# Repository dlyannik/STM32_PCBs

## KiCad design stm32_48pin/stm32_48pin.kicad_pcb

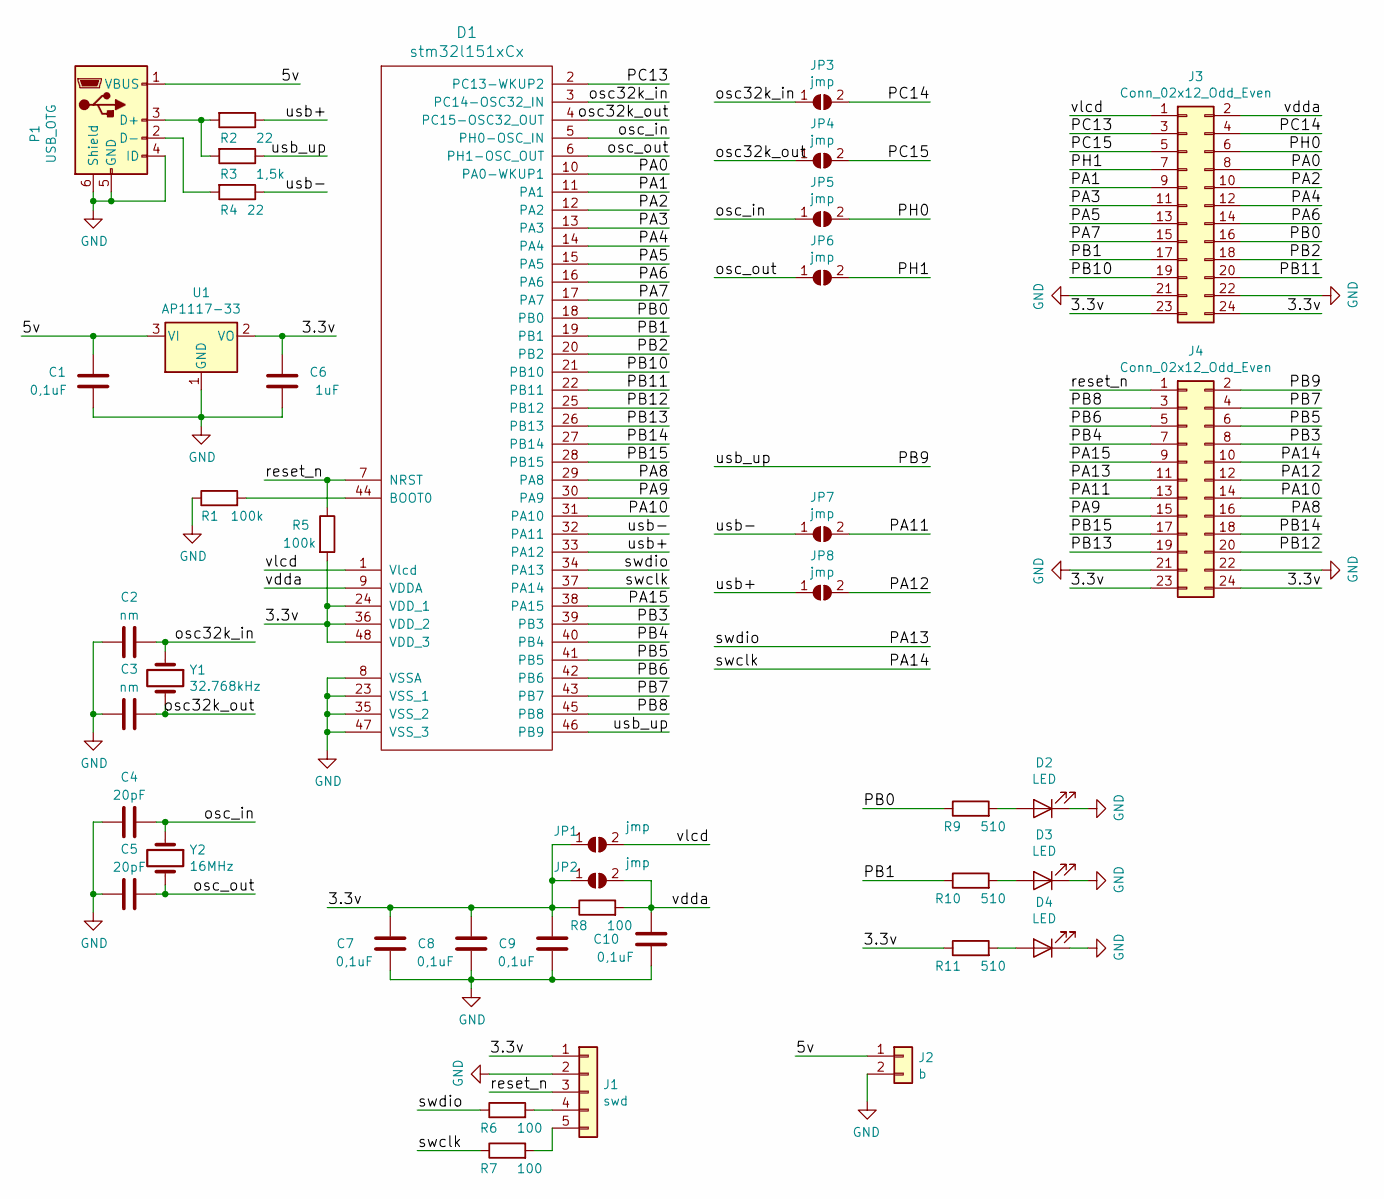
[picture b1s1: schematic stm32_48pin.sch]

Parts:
C1, C7, C8, C9, C10: 0,1uF; C_0603_1608Metric
C2, C3: nm; C_0603_1608Metric
C4, C5: 20pF; C_0603_1608Metric
C6: 1uF; C_0603_1608Metric
D1: stm32l151xCx; LQFP-48_7x7mm_P0.5mm
D2, D3, D4: LED; LED_0603_1608Metric
J1: swd; PinHeader_1x05_P2.54mm_Vertical
J2: b; PinHeader_1x02_P2.54mm_Vertical
J3, J4: Conn_02x12_Odd_Even; PinHeader_2x12_P2.54mm_Vertical
JP1, JP2, JP3, JP4, JP5, JP6, JP7, JP8: jmp; SolderJumper-2_P1.3mm_Open_TrianglePad1.0x1.5mm
P1: USB_OTG; USB_Mini-B_Lumberg_2486_01_Horizontal
R1, R5: 100k; R_0603_1608Metric
R2, R4: 22; R_0603_1608Metric
R3: 1,5k; R_0603_1608Metric
R6, R7, R8: 100; R_0603_1608Metric
R9, R10, R11: 510; R_0603_1608Metric
U1: AP1117-33; SOT-223-3_TabPin2
Y1: 32.768kHz; Crystal_DS26_D2.0mm_L6.0mm_Horizontal
Y2: 16MHz; Crystal_HC18-U_Vertical

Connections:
/3.3v: C6.1, C7.1, C8.1, C9.1, D1.24 (VDD_1), D1.36 (VDD_2), D1.48 (VDD_3), J1.1, J3.23, J3.24, J4.23, J4.24, JP1.1 (A), JP2.1 (A), R5.2, R8.1, R11.1, U1.2 (VO)
/5v: C1.1, J2.1, P1.1 (VBUS), U1.3 (VI)
/PA0: D1.10 (PA0-WKUP1), J3.8
/PA1: D1.11 (PA1), J3.9
/PA2: D1.12 (PA2), J3.10
/PA3: D1.13 (PA3), J3.11
/PA4: D1.14 (PA4), J3.12
/PA5: D1.15 (PA5), J3.13
/PA6: D1.16 (PA6), J3.14
/PA7: D1.17 (PA7), J3.15
/PA8: D1.29 (PA8), J4.16
/PA9: D1.30 (PA9), J4.15
/PA10: D1.31 (PA10), J4.14
/PA11: J4.13, JP7.2 (B)
/PA12: J4.12, JP8.2 (B)
/PA13: D1.34 (PA13), J4.11, R6.1
/PA14: D1.37 (PA14), J4.10, R7.1
/PA15: D1.38 (PA15), J4.9
/PB0: D1.18 (PB0), J3.16, R9.1
/PB1: D1.19 (PB1), J3.17, R10.1
/PB2: D1.20 (PB2), J3.18
/PB3: D1.39 (PB3), J4.8
/PB4: D1.40 (PB4), J4.7
/PB5: D1.41 (PB5), J4.6
/PB6: D1.42 (PB6), J4.5
/PB7: D1.43 (PB7), J4.4
/PB8: D1.45 (PB8), J4.3
/PB9: D1.46 (PB9), J4.2, R3.1
/PB10: D1.21 (PB10), J3.19
/PB11: D1.22 (PB11), J3.20
/PB12: D1.25 (PB12), J4.20
/PB13: D1.26 (PB13), J4.19
/PB14: D1.27 (PB14), J4.18
/PB15: D1.28 (PB15), J4.17
/PC13: D1.2 (PC13-WKUP2), J3.3
/PC14: J3.4, JP3.2 (B)
/PC15: J3.5, JP4.2 (B)
/PH0: J3.6, JP5.2 (B)
/PH1: J3.7, JP6.2 (B)
/osc32k_in: C2.1, D1.3 (PC14-OSC32_IN), JP3.1 (A), Y1.1
/osc32k_out: C3.1, D1.4 (PC15-OSC32_OUT), JP4.1 (A), Y1.2
/osc_in: C4.1, D1.5 (PH0-OSC_IN), JP5.1 (A), Y2.1
/osc_out: C5.1, D1.6 (PH1-OSC_OUT), JP6.1 (A), Y2.2
/reset_n: D1.7 (NRST), J1.3, J4.1, R5.1
/usb+: D1.33 (PA12), JP8.1 (A), R2.1
/usb-: D1.32 (PA11), JP7.1 (A), R4.1
/vdda: C10.1, D1.9 (VDDA), J3.2, JP2.2 (B), R8.2
/vlcd: D1.1 (Vlcd), J3.1, JP1.2 (B)
GND: C1.2, C2.2, C3.2, C4.2, C5.2, C6.2, C7.2, C8.2, C9.2, C10.2, D1.8 (VSSA), D1.23 (VSS_1), D1.35 (VSS_2), D1.47 (VSS_3), D2.1 (K), D3.1 (K), D4.1 (K), J1.2, J2.2, J3.21, J3.22, J4.21, J4.22, P1.4 (ID), P1.5 (GND), P1.6 (Shield), R1.1, U1.1 (GND)
unnamed: D1.44 (BOOT0), R1.2
unnamed: D2.2 (A), R9.2
unnamed: D3.2 (A), R10.2
unnamed: D4.2 (A), R11.2
unnamed: J1.4, R6.2
unnamed: J1.5, R7.2
unnamed: P1.2 (D-), R4.2
unnamed: P1.3 (D+), R2.2, R3.2

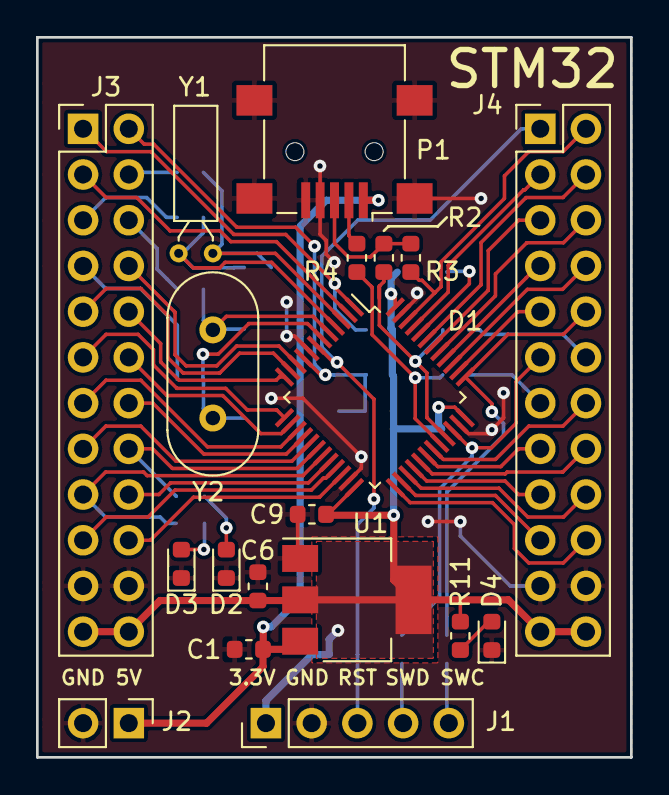
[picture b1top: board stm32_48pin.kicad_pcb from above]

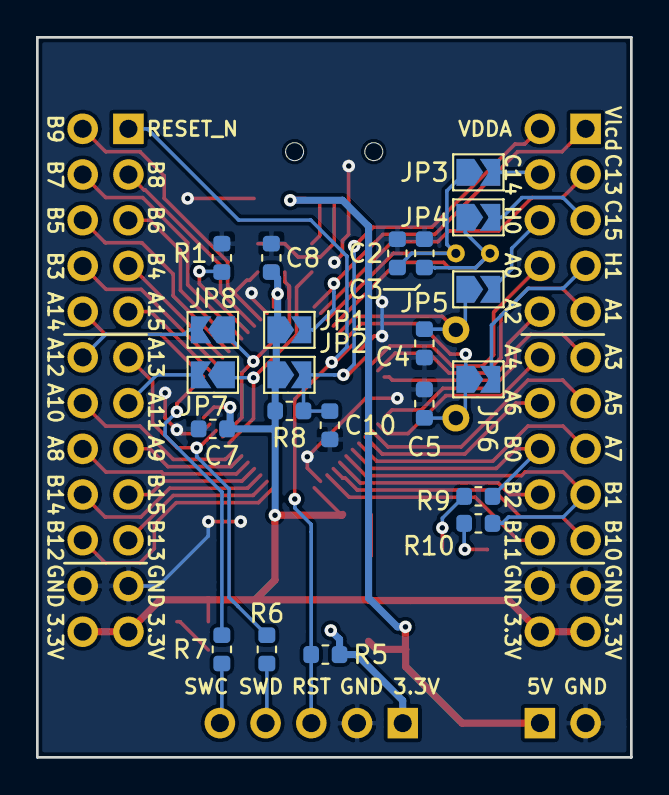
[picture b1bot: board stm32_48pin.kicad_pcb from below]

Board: 2 copper layers, 33.0 x 40.0 mm, 41 parts (22 on the bottom side), 57 nets.

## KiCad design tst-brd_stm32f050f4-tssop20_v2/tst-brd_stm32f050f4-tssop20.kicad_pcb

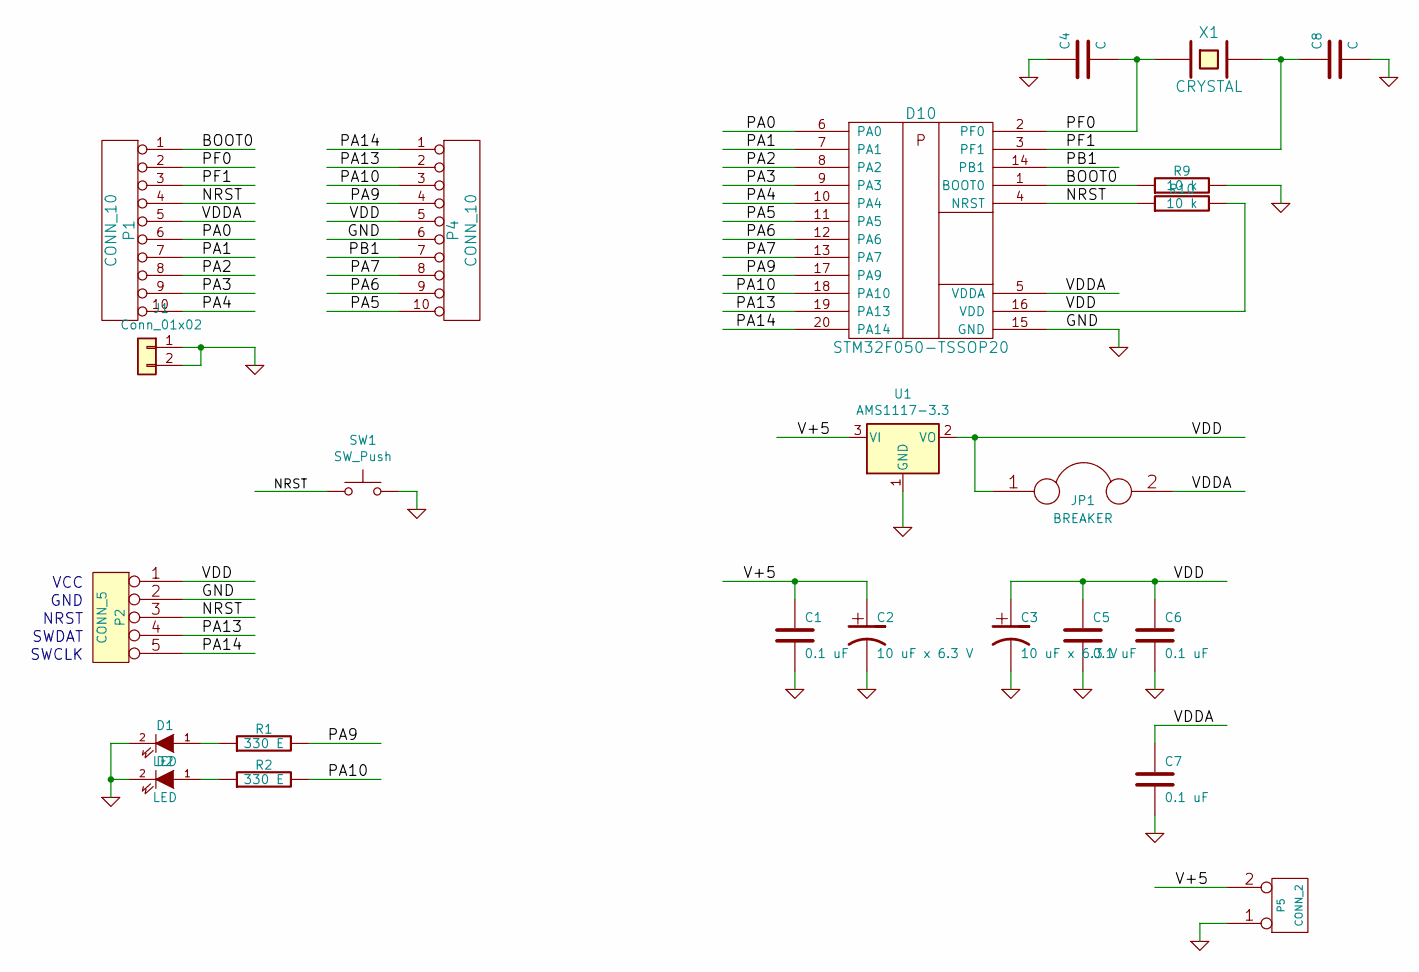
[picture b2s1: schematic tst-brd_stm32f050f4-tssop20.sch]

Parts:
C1, C5, C6, C7: 0.1 uF; C_0603_1608Metric
C2, C3: 10 uF x 6.3 V; CP_EIA-3528-21_Kemet-B_Pad1.50x2.35mm_HandSolder
C4, C8: C; C_0603_1608Metric
D1, D2: LED; LED_0603_1608Metric_Castellated
D10: STM32F050-TSSOP20; TSSOP-20_4.4x6.5mm_P0.65mm
J1: Conn_01x02; PinHeader_1x02_P2.54mm_Vertical
JP1: BREAKER; PinHeader_1x02_P2.54mm_Vertical
P1, P4: CONN_10; PinHeader_1x10_P2.54mm_Vertical
P2: CONN_5; PinHeader_1x05_P2.54mm_Vertical
P5: CONN_2; PinHeader_1x02_P2.54mm_Vertical
R1, R2: 330 E; R_0603_1608Metric
R9, R10: 10 k; R_0603_1608Metric
SW1: SW_Push; SW_SPST_FSMSM
U1: AMS1117-3.3; SOT-223-3_TabPin2
X1: CRYSTAL; Crystal_HC49-U_Vertical

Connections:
/BOOT0: D10.1 (BOOT0), P1.1, R9.1
/NRST: D10.4 (NRST), P1.4, P2.3, R10.1, SW1.1
/PA0: D10.6 (PA0), P1.6
/PA1: D10.7 (PA1), P1.7
/PA2: D10.8 (PA2), P1.8
/PA3: D10.9 (PA3), P1.9
/PA4: D10.10 (PA4), P1.10
/PA5: D10.11 (PA5), P4.10
/PA6: D10.12 (PA6), P4.9
/PA7: D10.13 (PA7), P4.8
/PA9: D10.17 (PA9), P4.4, R1.2
/PA10: D10.18 (PA10), P4.3, R2.2
/PA13: D10.19 (PA13), P2.4, P4.2
/PA14: D10.20 (PA14), P2.5, P4.1
/PB1: D10.14 (PB1), P4.7
/PF0: C4.2, D10.2 (PF0), P1.2, X1.1
/PF1: C8.1, D10.3 (PF1), P1.3, X1.2
/V+5: C1.1, C2.1, P5.2 (PM), U1.3 (VI)
/VDD: C3.1, C5.1, C6.1, D10.16 (VDD), JP1.1, P2.1, P4.5, R10.2, U1.2 (VO)
/VDDA: C7.1, D10.5 (VDDA), JP1.2, P1.5
GND: C1.2, C2.2, C3.2, C4.1, C5.2, C6.2, C7.2, C8.2, D1.2 (K), D2.2 (K), D10.15 (GND), J1.1, J1.2, P2.2, P4.6, P5.1, R9.2, SW1.2, U1.1 (GND)
unnamed: D1.1 (A), R1.1
unnamed: D2.1 (A), R2.1

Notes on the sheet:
SWDAT
GND
SWCLK
VCC
NRST

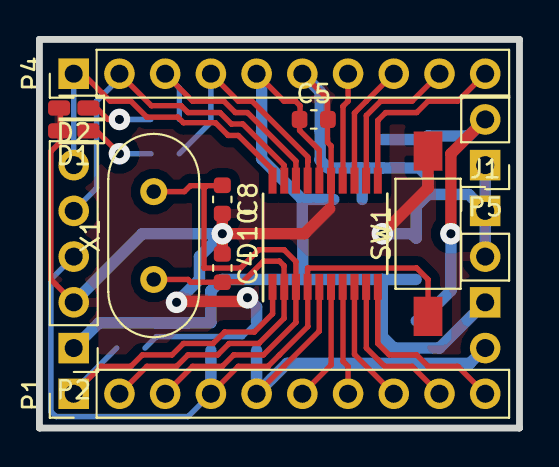
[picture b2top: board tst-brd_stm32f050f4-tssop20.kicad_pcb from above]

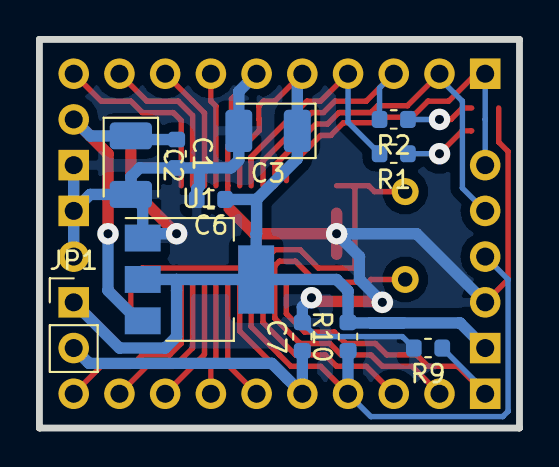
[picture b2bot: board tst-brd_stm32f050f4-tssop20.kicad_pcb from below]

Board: 2 copper layers, 26.7 x 21.6 mm, 24 parts (11 on the bottom side), 23 nets.

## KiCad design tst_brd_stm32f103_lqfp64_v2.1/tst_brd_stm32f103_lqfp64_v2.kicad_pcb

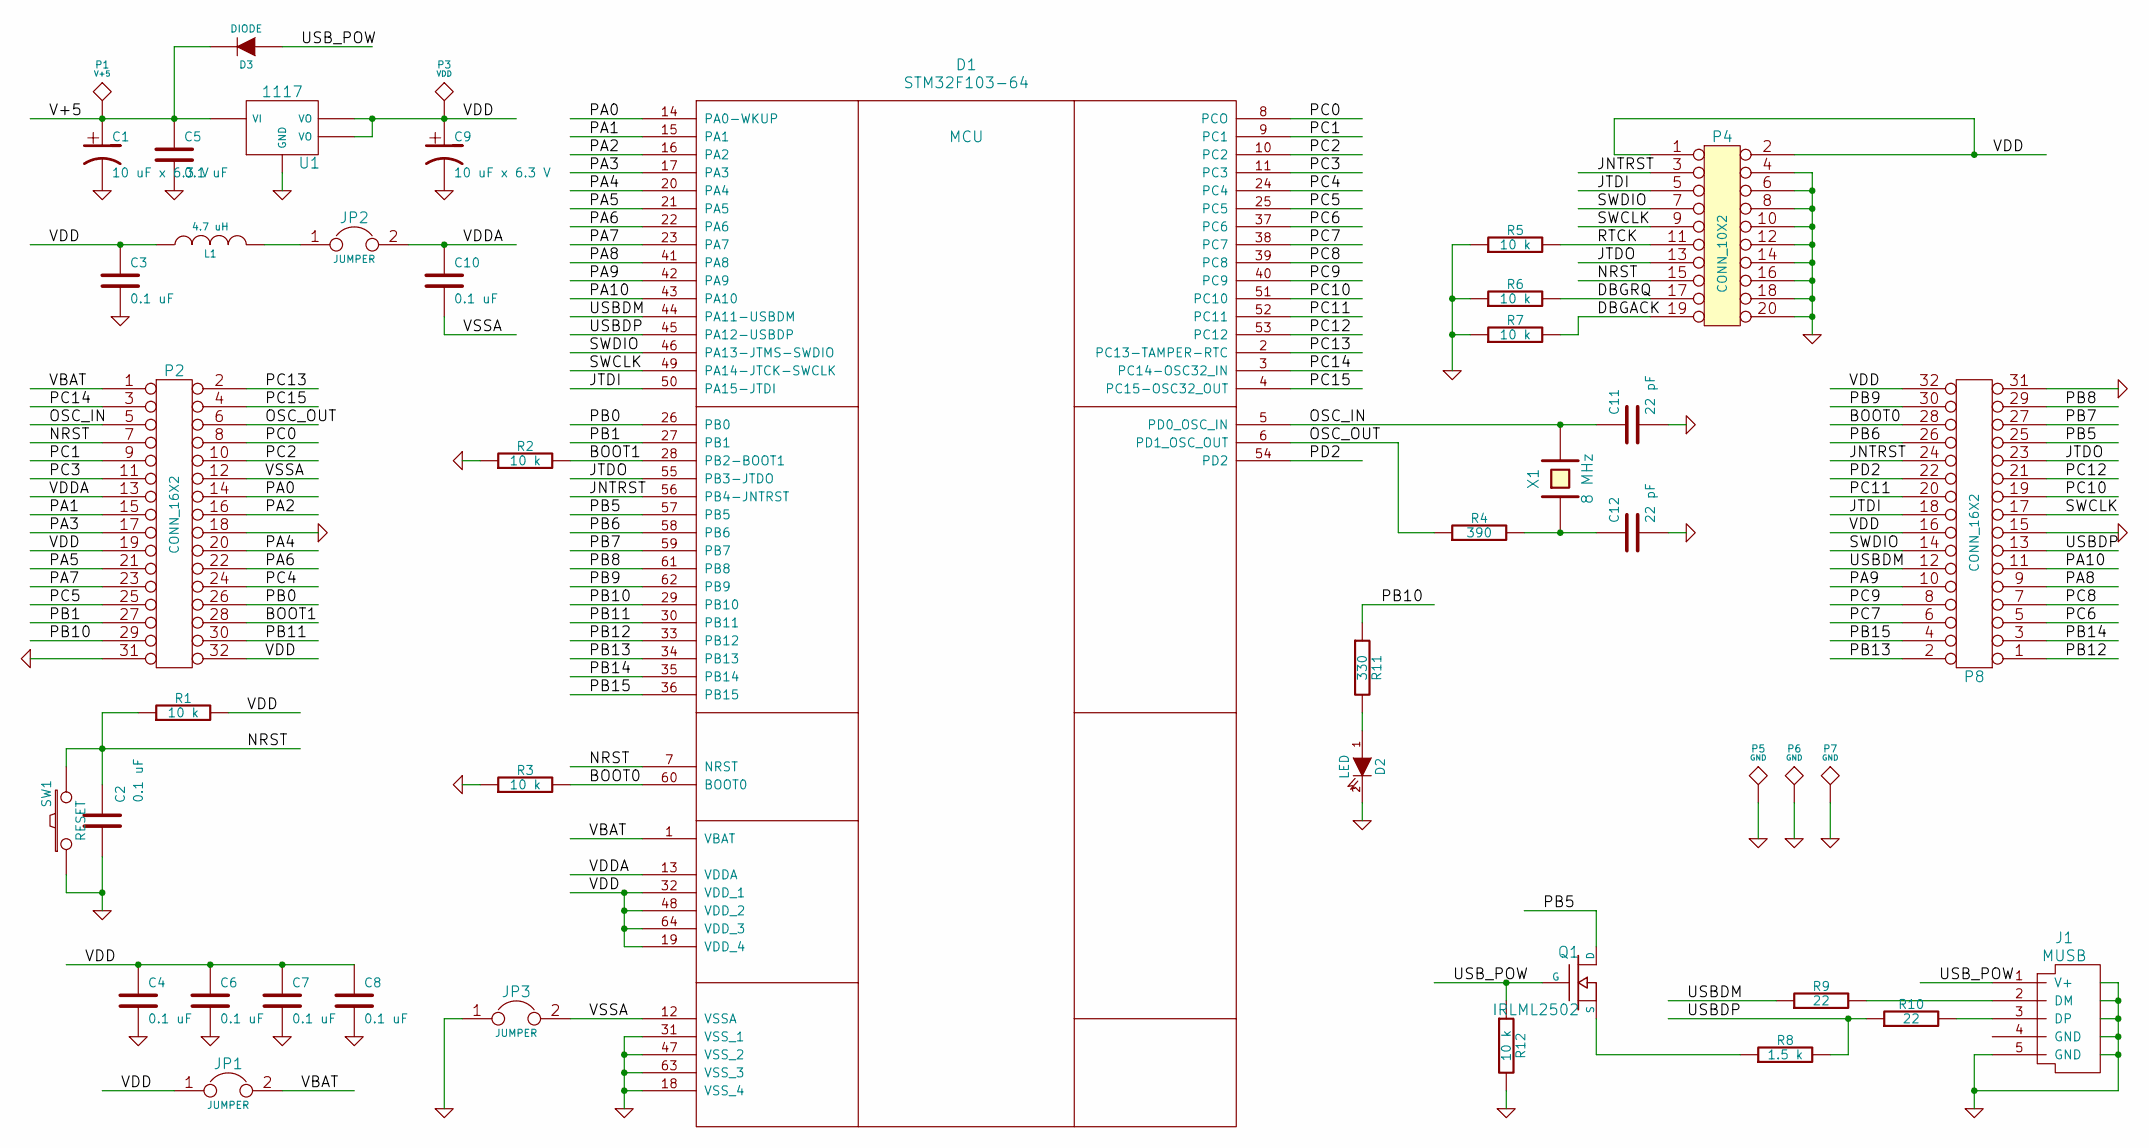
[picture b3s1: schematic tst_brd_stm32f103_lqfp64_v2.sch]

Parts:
C1, C9: 10 uF x 6.3 V; CP_EIA-3528-21_Kemet-B_Pad1.50x2.35mm_HandSolder
C2, C3, C4, C5, C6, C7, C8, C10: 0.1 uF; C_0603_1608Metric
C11, C12: 22 pF; C_0603_1608Metric
D1: STM32F103-64; TQFP-64_10x10mm_P0.5mm
D2: LED; LED_D3.0mm
D3: DIODE; D_1806_4516Metric_Pad1.57x1.80mm_HandSolder
J1: MUSB; USB_Mini-B_Lumberg_2486_01_Horizontal
JP1, JP2, JP3: JUMPER; PinHeader_1x02_P2.54mm_Vertical
L1: 4.7 uH; L_0603_1608Metric
P1: V+5; PinHeader_1x01_P2.54mm_Vertical
P2, P8: CONN_16X2; PinHeader_2x16_P2.54mm_Vertical
P3: VDD; PinHeader_1x01_P2.54mm_Vertical
P4: CONN_10X2; PinHeader_2x10_P2.54mm_Vertical
P5, P6, P7: GND; PinHeader_1x01_P2.54mm_Vertical
Q1: IRLML2502; SOT-23
R1, R2, R3, R5, R6, R7, R12: 10 k; R_0603_1608Metric
R4: 390; R_0603_1608Metric
R8: 1.5 k; R_0603_1608Metric
R9, R10: 22; R_0603_1608Metric
R11: 330; R_0603_1608Metric
SW1: RESET; SW_PUSH_6mm
U1: 1117; SOT-223-3_TabPin2
X1: 8 MHz; Crystal_HC49-U_Vertical

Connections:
/BOOT0: D1.60 (BOOT0), P8.28, R3.2
/BOOT1: D1.28 (PB2-BOOT1), P2.28, R2.2
/DBGACK: P4.19, R7.2
/DBGRQ: P4.17, R6.2
/JNTRST: D1.56 (PB4-JNTRST), P4.3, P8.24
/JTDI: D1.50 (PA15-JTDI), P4.5, P8.18
/JTDO: D1.55 (PB3-JTDO), P4.13, P8.23
/NRST: C2.2, D1.7 (NRST), P2.7, P4.15, R1.1, SW1.2
/OSC_IN: C11.1, D1.5 (PD0_OSC_IN), P2.5, X1.2
/OSC_OUT: D1.6 (PD1_OSC_OUT), P2.6, R4.1
/PA0: D1.14 (PA0-WKUP), P2.14
/PA1: D1.15 (PA1), P2.15
/PA2: D1.16 (PA2), P2.16
/PA3: D1.17 (PA3), P2.17
/PA4: D1.20 (PA4), P2.20
/PA5: D1.21 (PA5), P2.21
/PA6: D1.22 (PA6), P2.22
/PA7: D1.23 (PA7), P2.23
/PA8: D1.41 (PA8), P8.9
/PA9: D1.42 (PA9), P8.10
/PA10: D1.43 (PA10), P8.11
/PB0: D1.26 (PB0), P2.26
/PB1: D1.27 (PB1), P2.27
/PB5: D1.57 (PB5), P8.25, Q1.3 (D)
/PB6: D1.58 (PB6), P8.26
/PB7: D1.59 (PB7), P8.27
/PB8: D1.61 (PB8), P8.29
/PB9: D1.62 (PB9), P8.30
/PB10: D1.29 (PB10), P2.29, R11.1
/PB11: D1.30 (PB11), P2.30
/PB12: D1.33 (PB12), P8.1
/PB13: D1.34 (PB13), P8.2
/PB14: D1.35 (PB14), P8.3
/PB15: D1.36 (PB15), P8.4
/PC0: D1.8 (PCO), P2.8
/PC1: D1.9 (PC1), P2.9
/PC2: D1.10 (PC2), P2.10
/PC3: D1.11 (PC3), P2.11
/PC4: D1.24 (PC4), P2.24
/PC5: D1.25 (PC5), P2.25
/PC6: D1.37 (PC6), P8.5
/PC7: D1.38 (PC7), P8.6
/PC8: D1.39 (PC8), P8.7
/PC9: D1.40 (PC9), P8.8
/PC10: D1.51 (PC10), P8.19
/PC11: D1.52 (PC11), P8.20
/PC12: D1.53 (PC12), P8.21
/PC13: D1.2 (PC13-TAMPER-RTC), P2.2
/PC14: D1.3 (PC14-OSC32_IN), P2.3
/PC15: D1.4 (PC15-OSC32_OUT), P2.4
/PD2: D1.54 (PD2), P8.22
/RTCK: P4.11, R5.2
/SWCLK: D1.49 (PA14-JTCK-SWCLK), P4.9, P8.17
/SWDIO: D1.46 (PA13-JTMS-SWDIO), P4.7, P8.14
/USBDM: D1.44 (PA11-USBDM), P8.12, R9.1
/USBDP: D1.45 (PA12-USBDP), P8.13, R8.2, R10.1
/USB_POW: D3.1 (A), J1.1 (V+), Q1.1 (G), R12.1
/V+5: C1.1, C5.1, D3.2 (K), P1.1, U1.3 (VI)
/VBAT: D1.1 (VBAT), JP1.2, P2.1
/VDD: C3.1, C4.1, C6.1, C7.1, C8.1, C9.1, D1.19 (VDD_4), D1.32 (VDD_1), D1.48 (VDD_2), D1.64 (VDD_3), JP1.1, L1.1, P2.19, P2.32, P3.1, P4.1, P4.2, P8.16, P8.32, R1.2, U1.2 (VO), U1.4 (VO)
/VDDA: C10.1, D1.13 (VDDA), JP2.2, P2.13
/VSSA: C10.2, D1.12 (VSSA), JP3.2, P2.12
GND: C1.2, C2.1, C3.2, C4.2, C5.2, C6.2, C7.2, C8.2, C9.2, C11.2, C12.2, D1.18 (VSS_4), D1.31 (VSS_1), D1.47 (VSS_2), D1.63 (VSS_3), D2.2 (K), J1.5 (GND), J1.6 (GND), J1.7 (GND), J1.8 (GND), J1.9 (GND), J1.10 (GND), JP3.1, P2.18, P2.31, P4.4, P4.6, P4.8, P4.10, P4.12, P4.14, P4.16, P4.18, P4.20, P5.1, P6.1, P7.1, P8.15, P8.31, R2.1, R3.1, R5.1, R6.1, R7.1, R12.2, SW1.1, U1.1 (GND)
unnamed: C12.1, R4.2, X1.1
unnamed: D2.1 (A), R11.2
unnamed: J1.2 (DM), R9.2
unnamed: J1.3 (DP), R10.2
unnamed: JP2.1, L1.2
unnamed: Q1.2 (S), R8.1

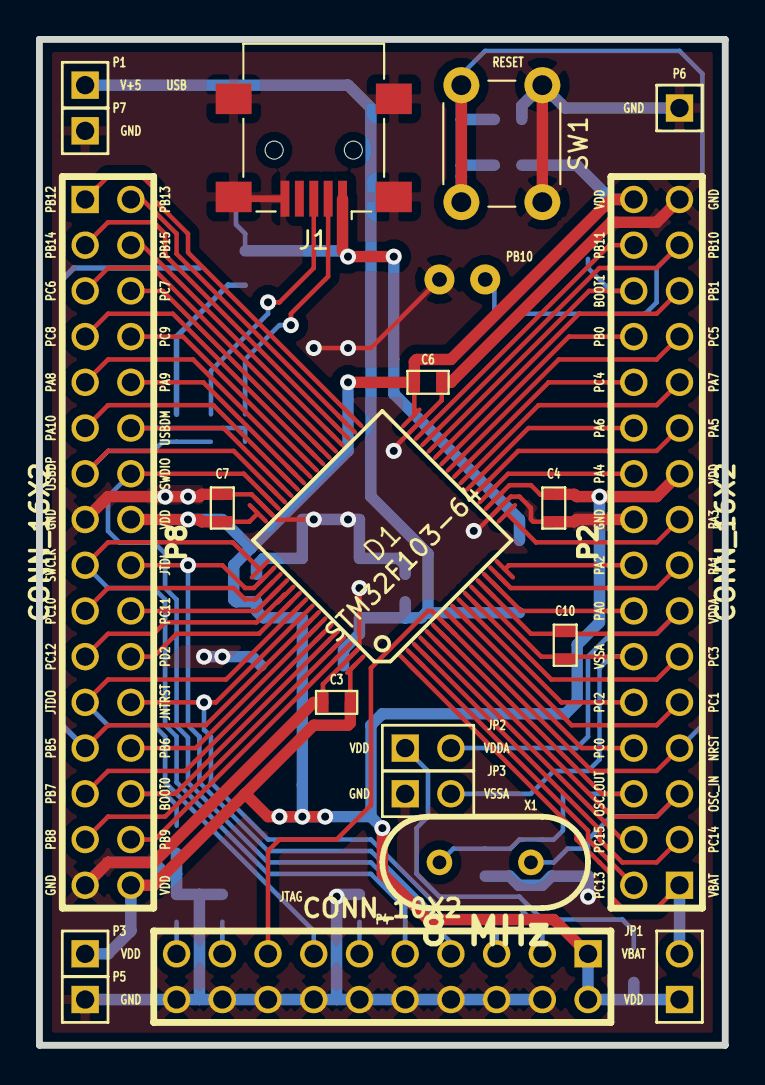
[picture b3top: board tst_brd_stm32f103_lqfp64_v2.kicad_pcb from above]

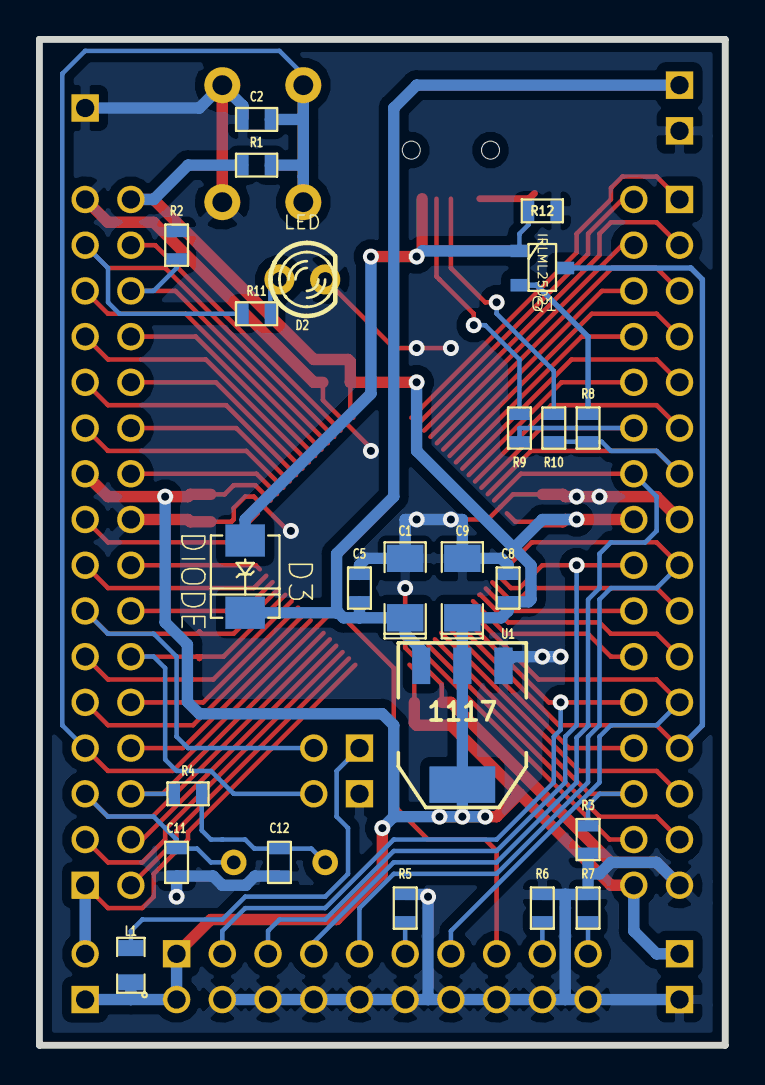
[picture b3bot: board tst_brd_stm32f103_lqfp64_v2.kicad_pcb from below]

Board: 2 copper layers, 38.1 x 55.9 mm, 44 parts (24 on the bottom side), 69 nets.

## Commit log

2019-02-05 Added 3 pcb
